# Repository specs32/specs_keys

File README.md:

# specs_keys - REV 1 (confirmed working, typing on it now :D)

### TKL ISO keyboard based on an g80-3000HAD running QMK

15 Years ago I found 2 g80-3000 HAD Keyboards in the trash, one broke lately so I designed a PCB to mount these sweet sweet Cherry MX black switches on it.

The base plate is the acryl plate from an old TFT Monitor cut to size and sanded. (roughly)
Between PCB and baseplate is some foamy stuff for dampening.

So, except the pcb and the mcu and a couple smd parts this thing is completly salvaged from trash.

Overall cost per board with parts (except switches) : 18 €

(8 € per PCB and 10 € for SMD parts, rest is salvaged, so this is probably the cheapest build out there)

Features  :
  - ATMega 32U4 @ 8 MHz (why the crystal ... such a waste, sigh)
  - USB-C jack **with FUSE and full ESD protection** (gnd vcc d+ d-)
  - MOSFET controlled bottom backlighting pads for 14 LEDs with resistors plus 2 extra 2mm connectors for lantern style lightning
  - Scroll and caps indicators (active low atm.. I kinda like it)
  - SPI interface and reset
  - 340mA overall power consumption with full lights (I put in UV / pink LEDs and 14 Ω Resistors)

the QMK layout and config can be found here :  https://github.com/specs32/specs_keys/tree/main/specskeys

I hex the MCU with avrdude from cli after QMK compile, somehow I had trouble with bootloaders all my life ^^ (also safer this way .. I guess;))

> qmk_firmware [master]× » avrdude -c usbasp -p m32u4 -B10 -U lfuse:w:0xD2:m -U hfuse:w:0x98:m -U efuse:w:0xFF:m

> qmk_firmware [master]× » avrdude -c usbasp -pm32u4 -B10 -Uflash:w:.build/specskeys_default.hex                

designed with kicad nightly Version: (5.99.0-10004-g132ec37b56), release build
and some gimp

credits :

- evyd13 and ebastler (to modify the g80-3003 design was my initial attempt but I did build the PCB from scratch then)
- the designers of evil80 (whoever that might be, couldn't find any infos on that) I used some of their qmk layout information as info for mine

License on the KiCAD Design files : ♥ CC-BY-SA-4.0

All other parts of this build inherit their Licenses from their origin.

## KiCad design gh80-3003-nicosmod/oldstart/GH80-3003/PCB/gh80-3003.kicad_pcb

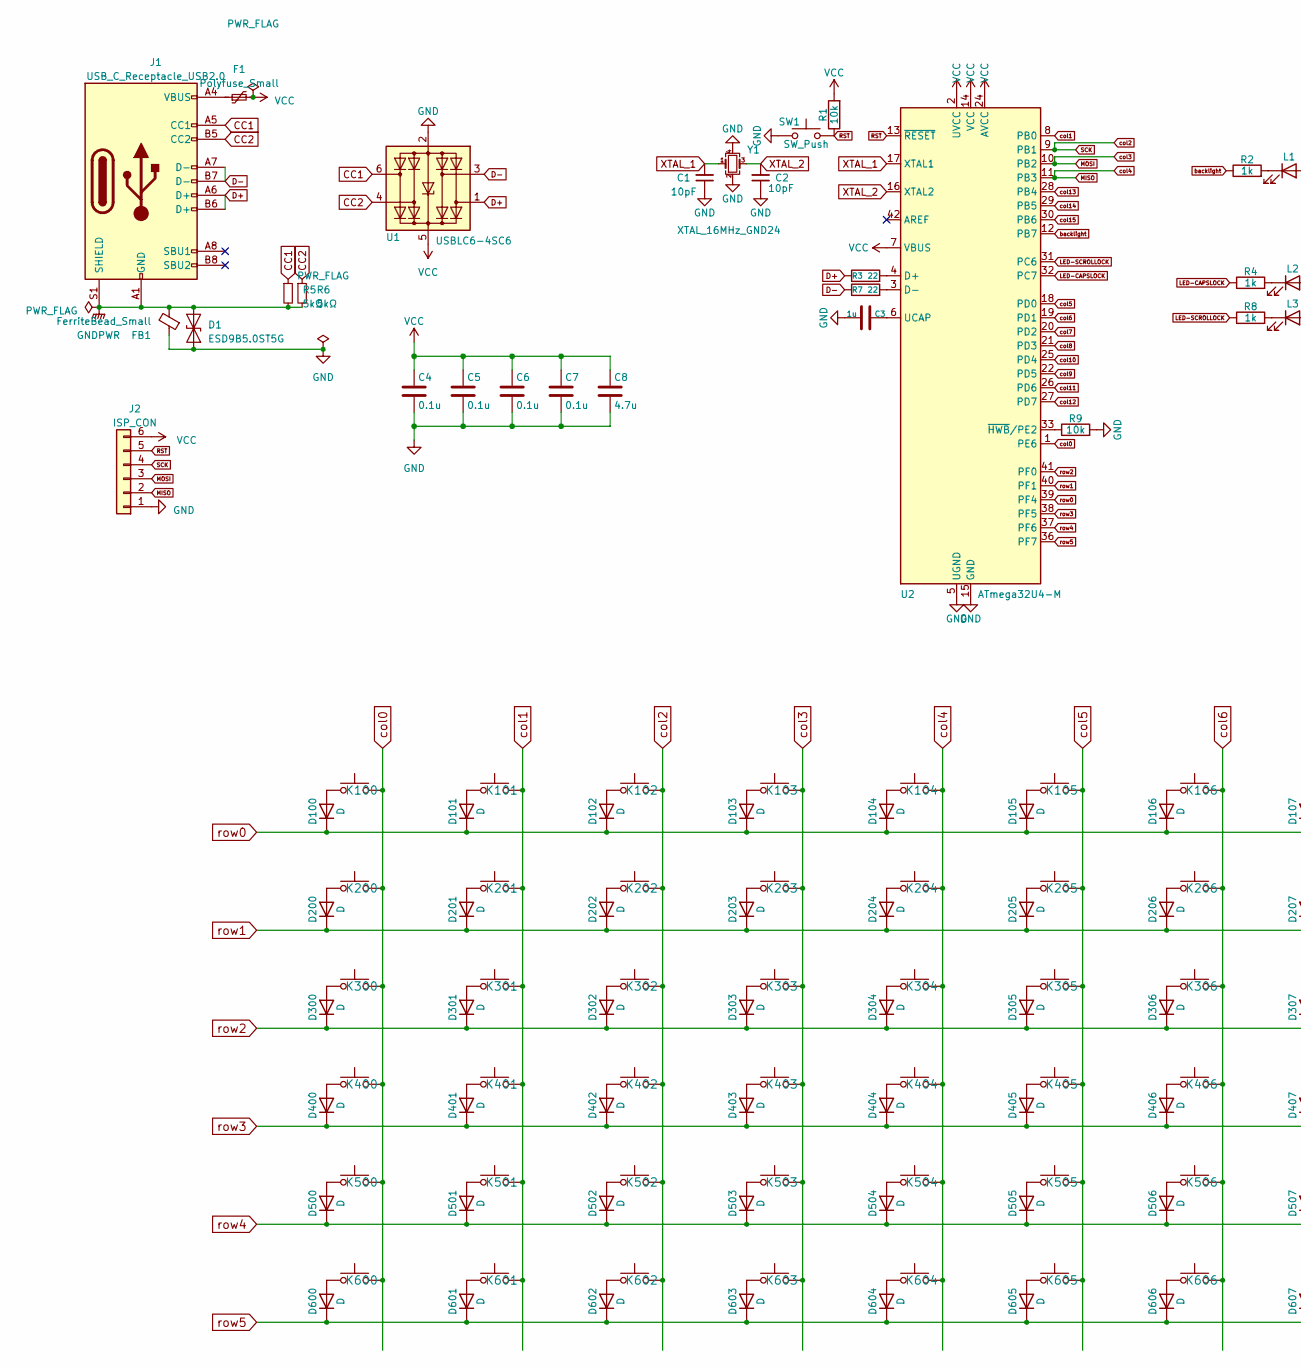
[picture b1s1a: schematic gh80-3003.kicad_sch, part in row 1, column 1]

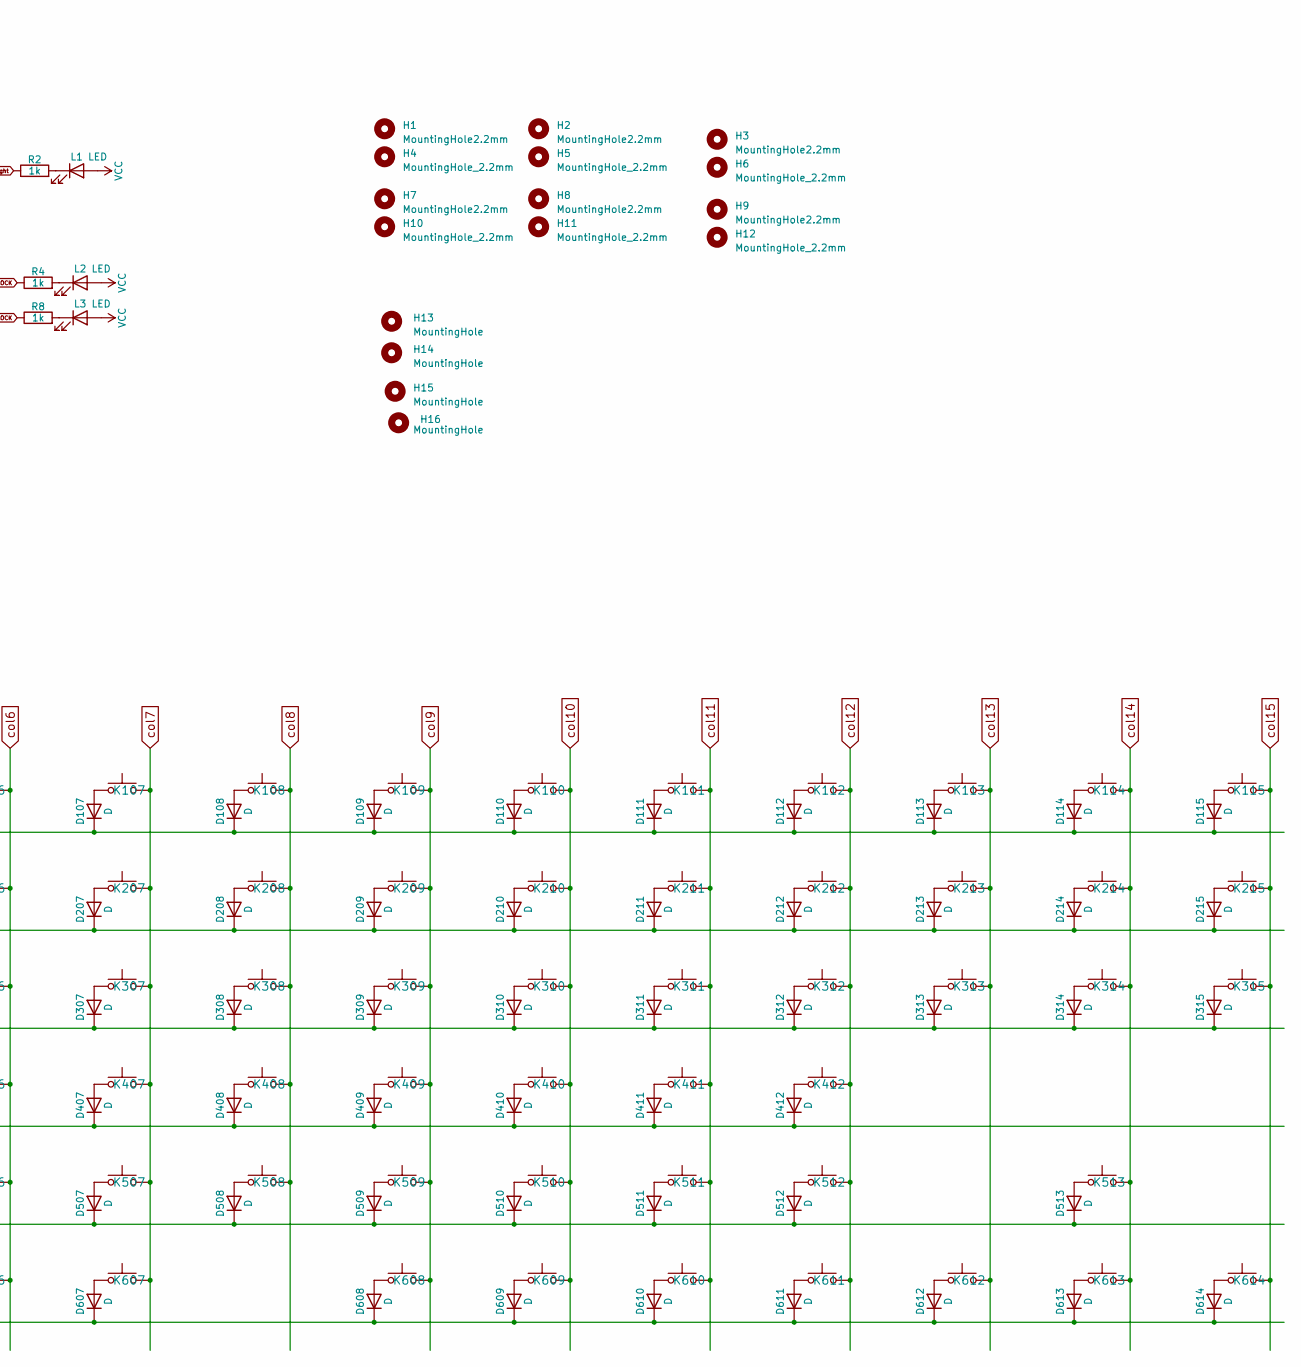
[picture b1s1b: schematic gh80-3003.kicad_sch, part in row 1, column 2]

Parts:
C1, C2: 10pF; C_0603_1608Metric_Pad1.08x0.95mm_HandSolder
C3: 1u; C_0805_2012Metric_Pad1.18x1.45mm_HandSolder
C4, C5, C6, C7: 0.1u; C_0603_1608Metric
C8: 4.7u; C_0805_2012Metric_Pad1.18x1.45mm_HandSolder
D1: ESD9B5.0ST5G; D_0402_1005Metric_Pad0.77x0.64mm_HandSolder
D100, D101, D102, D103, D104, D105, D106, D107, D108, D109, D110, D111, D112, D113, D114, D115, D200, D201, D202, D203, D204, D205, D206, D207, D208, D209, D210, D211, D212, D213, D214, D215, D300, D301, D302, D303, D304, D305, D306, D307, D308, D309, D310, D311, D312, D313, D314, D315, D400, D401, D402, D403, D404, D405, D406, D407, D408, D409, D410, D411, D412, D500, D501, D502, D503, D504, D505, D506, D507, D508, D509, D510, D511, D512, D513, D600, D601, D602, D603, D604, D605, D606, D607, D608, D609, D610, D611, D612, D613, D614: D; D_0402_1005Metric_Pad0.77x0.64mm_HandSolder
F1: Polyfuse_Small; R_0805_2012Metric_Pad1.20x1.40mm_HandSolder
FB1: FerriteBead_Small; R_0805_2012Metric_Pad1.20x1.40mm_HandSolder
H1, H2, H3, H7, H8, H9: MountingHole2.2mm; MountingHole_2.2mm_M2
H4, H5, H6, H10, H11, H12: MountingHole_2.2mm; MountingHole_2.2mm_M2
H13, H14, H15, H16: MountingHole; MountingHole_5.3mm_M5_ISO14580
J1: USB_C_Receptacle_USB2.0; USB_C_Receptacle_JAE_DX07S016JA1R1500
J2: ISP_CON; Conn_01x06_SMD_2mm
K100, K101, K102, K103, K104, K105, K106, K107, K108, K109, K110, K111, K112, K113, K114, K115, K200, K201, K202, K203, K204, K205, K206, K207, K208, K209, K210, K211, K212, K213, K214, K215, K300, K301, K302, K303, K304, K305, K306, K307, K308, K309, K310, K311, K312, K313, K314, K315, K400, K401, K402, K403, K404, K405, K406, K407, K408, K409, K410, K411, K412, K500, K501, K502, K503, K504, K505, K506, K507, K508, K509, K510, K511, K512, K513, K600, K605, K606, K607, K608, K609, K610, K611, K612, K613, K614: SW_Push; SW_Cherry_MX_1.00u_PCB
K601, K603: SW_Push; SW_Cherry_MX_1.50u_PCB
K602: SW_Push; SW_Cherry_MX_2.00u_PCB
K604: SW_Push; SW_Cherry_MX_1.75u_PCB
L1, L2, L3: LED; LED_0805_2012Metric_Pad1.15x1.40mm_HandSolder
R1, R9: 10k; R_0603_1608Metric
R2, R4, R8: 1k; R_0603_1608Metric
R3, R7: 22; R_0603_1608Metric
R5, R6: 5kΩ; R_0603_1608Metric
SW1: SW_Push; SW_SPST_TL3342
U1: USBLC6-4SC6; SOT-23-6
U2: ATmega32U4-M; QFN-44-1EP_7x7mm_P0.5mm_EP5.2x5.2mm
Y1: XTAL_16MHz_GND24; Crystal_SMD_2016-4Pin_2.0x1.6mm

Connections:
CC1: J1.A5 (CC1), R5.1, U1.6 (I/O4)
CC2: J1.B5 (CC2), R6.1, U1.4 (I/O3)
D+: J1.A6 (D+), J1.B6 (D+), R3.1, U1.1 (I/O1)
D-: J1.A7 (D-), J1.B7 (D-), R7.1, U1.3 (I/O2)
GND: C1.1, C2.1, C3.2, C4.2, C5.2, C6.2, C7.2, C8.2, D1.1 (A1), FB1.1, J2.1, R9.2, SW1.1, U1.2 (GND), U2.5 (UGND), U2.15 (GND), U2.23 (GND), U2.35 (GND), U2.43 (GND), U2.45 (GND), Y1.2, Y1.4
GNDPWR: D1.2 (A2), FB1.2, J1.A1 (GND), J1.A12 (GND), J1.B1 (GND), J1.B12 (GND), J1.S1 (SHIELD), R5.2, R6.2
LED-CAPSLOCK: R4.1, U2.32 (PC7)
LED-SCROLLOCK: R8.1, U2.31 (PC6)
MISO: J2.2, K104.1, K204.1, K304.1, K404.1, K504.1, K604.1, U2.11 (PB3)
MOSI: J2.3, K103.1, K203.1, K303.1, K403.1, K503.1, K603.1, U2.10 (PB2)
unnamed: C3.1, U2.6 (UCAP)
unnamed: D100.2 (A), K100.2
unnamed: D101.2 (A), K101.2
unnamed: D102.2 (A), K102.2
unnamed: D103.2 (A), K103.2
unnamed: D104.2 (A), K104.2
unnamed: D105.2 (A), K105.2
unnamed: D106.2 (A), K106.2
unnamed: D107.2 (A), K107.2
unnamed: D108.2 (A), K108.2
unnamed: D109.2 (A), K109.2
unnamed: D110.2 (A), K110.2
unnamed: D111.2 (A), K111.2
unnamed: D112.2 (A), K112.2
unnamed: D113.2 (A), K113.2
unnamed: D114.2 (A), K114.2
unnamed: D115.2 (A), K115.2
unnamed: D200.2 (A), K200.2
unnamed: D201.2 (A), K201.2
unnamed: D203.2 (A), K203.2
unnamed: D205.2 (A), K205.2
unnamed: D206.2 (A), K206.2
unnamed: D207.2 (A), K207.2
unnamed: D209.2 (A), K209.2
unnamed: D210.2 (A), K210.2
unnamed: D211.2 (A), K211.2
unnamed: D212.2 (A), K212.2
unnamed: D213.2 (A), K213.2
unnamed: D214.2 (A), K214.2
unnamed: D215.2 (A), K215.2
unnamed: D300.2 (A), K300.2
unnamed: D301.2 (A), K301.2
unnamed: D302.2 (A), K302.2
unnamed: D303.2 (A), K303.2
unnamed: D304.2 (A), K304.2
unnamed: D305.2 (A), K305.2
unnamed: D306.2 (A), K306.2
unnamed: D307.2 (A), K307.2
unnamed: D308.2 (A), K308.2
unnamed: D309.2 (A), K309.2
unnamed: D310.2 (A), K310.2
unnamed: D311.2 (A), K311.2
unnamed: D312.2 (A), K312.2
unnamed: D313.2 (A), K313.2
unnamed: D314.2 (A), K314.2
unnamed: D315.2 (A), K315.2
unnamed: D400.2 (A), K400.2
unnamed: D401.2 (A), K401.2
unnamed: D402.2 (A), K402.2
unnamed: D403.2 (A), K403.2
unnamed: D404.2 (A), K404.2
unnamed: D405.2 (A), K405.2
unnamed: D406.2 (A), K406.2
unnamed: D407.2 (A), K407.2
unnamed: D408.2 (A), K408.2
unnamed: D409.2 (A), K409.2
unnamed: D410.2 (A), K410.2
unnamed: D411.2 (A), K411.2
unnamed: D412.2 (A), K412.2
unnamed: D500.2 (A), K500.2
unnamed: D501.2 (A), K501.2
unnamed: D502.2 (A), K502.2
unnamed: D503.2 (A), K503.2
unnamed: D504.2 (A), K504.2
unnamed: D505.2 (A), K505.2
unnamed: D506.2 (A), K506.2
unnamed: D507.2 (A), K507.2
unnamed: D508.2 (A), K508.2
unnamed: D509.2 (A), K509.2
unnamed: D510.2 (A), K510.2
unnamed: D511.2 (A), K511.2
unnamed: D512.2 (A), K512.2
unnamed: D513.2 (A), K513.2
unnamed: D600.2 (A), K600.2
unnamed: D601.2 (A), K601.2
unnamed: D602.2 (A), K602.2
unnamed: D603.2 (A), K603.2
unnamed: D604.2 (A), K604.2
unnamed: D605.2 (A), K605.2
unnamed: D606.2 (A), K606.2
unnamed: D607.2 (A), K607.2
unnamed: D608.2 (A), K608.2
unnamed: D609.2 (A), K609.2
unnamed: D610.2 (A), K610.2
unnamed: D611.2 (A), K611.2
unnamed: D612.2 (A), K612.2
unnamed: D613.2 (A), K613.2
unnamed: D614.2 (A), K614.2
unnamed: F1.1, J1.A4 (VBUS), J1.A9 (VBUS), J1.B4 (VBUS), J1.B9 (VBUS)
unnamed: D202.2 (A), K202.2
unnamed: D204.2 (A), K204.2
unnamed: D208.2 (A), K208.2
unnamed: L1.1 (K), R2.2
unnamed: L2.1 (K), R4.2
unnamed: L3.1 (K), R8.2
unnamed: R3.2, U2.4 (D+)
unnamed: R7.2, U2.3 (D-)
unnamed: R9.1, U2.33 (~HWB~/PE2)
RST: J2.5, R1.1, SW1.2, U2.13 (~RESET)
SCK: J2.4, K102.1, K202.1, K302.1, K402.1, K502.1, K602.1, U2.9 (PB1)
VCC: C4.1, C5.1, C6.1, C7.1, C8.1, F1.2, J2.6, L1.2 (A), L2.2 (A), L3.2 (A), R1.2, U1.5 (VBUS), U2.2 (UVCC), U2.7 (VBUS), U2.14 (VCC), U2.24 (AVCC), U2.34 (VCC), U2.44 (AVCC)
XTAL_1: C1.2, U2.17 (XTAL1), Y1.1
XTAL_2: C2.2, U2.16 (XTAL2), Y1.3
backlight: R2.1, U2.12 (PB7)
col0: K100.1, K200.1, K300.1, K400.1, K500.1, K600.1, U2.1 (PE6)
col1: K101.1, K201.1, K301.1, K401.1, K501.1, K601.1, U2.8 (PB0)
col5: K105.1, K205.1, K305.1, K405.1, K505.1, K605.1, U2.18 (PD0)
col6: K106.1, K206.1, K306.1, K406.1, K506.1, K606.1, U2.19 (PD1)
col7: K107.1, K207.1, K307.1, K407.1, K507.1, K607.1, U2.20 (PD2)
col8: K108.1, K208.1, K308.1, K408.1, K508.1, U2.21 (PD3)
col9: K109.1, K209.1, K309.1, K409.1, K509.1, K608.1, U2.22 (PD5)
col10: K110.1, K210.1, K310.1, K410.1, K510.1, K609.1, U2.25 (PD4)
col11: K111.1, K211.1, K311.1, K411.1, K511.1, K610.1, U2.26 (PD6)
col12: K112.1, K212.1, K312.1, K412.1, K512.1, K611.1, U2.27 (PD7)
col13: K113.1, K213.1, K313.1, K612.1, U2.28 (PB4)
col14: K114.1, K214.1, K314.1, K513.1, K613.1, U2.29 (PB5)
col15: K115.1, K215.1, K315.1, K614.1, U2.30 (PB6)
row0: D100.1 (K), D101.1 (K), D102.1 (K), D103.1 (K), D104.1 (K), D105.1 (K), D106.1 (K), D107.1 (K), D108.1 (K), D109.1 (K), D110.1 (K), D111.1 (K), D112.1 (K), D113.1 (K), D114.1 (K), D115.1 (K), U2.39 (PF4)
row1: D200.1 (K), D201.1 (K), D202.1 (K), D203.1 (K), D204.1 (K), D205.1 (K), D206.1 (K), D207.1 (K), D208.1 (K), D209.1 (K), D210.1 (K), D211.1 (K), D212.1 (K), D213.1 (K), D214.1 (K), D215.1 (K), U2.40 (PF1)
row2: D300.1 (K), D301.1 (K), D302.1 (K), D303.1 (K), D304.1 (K), D305.1 (K), D306.1 (K), D307.1 (K), D308.1 (K), D309.1 (K), D310.1 (K), D311.1 (K), D312.1 (K), D313.1 (K), D314.1 (K), D315.1 (K), U2.41 (PF0)
row3: D400.1 (K), D401.1 (K), D402.1 (K), D403.1 (K), D404.1 (K), D405.1 (K), D406.1 (K), D407.1 (K), D408.1 (K), D409.1 (K), D410.1 (K), D411.1 (K), D412.1 (K), U2.38 (PF5)
row4: D500.1 (K), D501.1 (K), D502.1 (K), D503.1 (K), D504.1 (K), D505.1 (K), D506.1 (K), D507.1 (K), D508.1 (K), D509.1 (K), D510.1 (K), D511.1 (K), D512.1 (K), D513.1 (K), U2.37 (PF6)
row5: D600.1 (K), D601.1 (K), D602.1 (K), D603.1 (K), D604.1 (K), D605.1 (K), D606.1 (K), D607.1 (K), D608.1 (K), D609.1 (K), D610.1 (K), D611.1 (K), D612.1 (K), D613.1 (K), D614.1 (K), U2.36 (PF7)

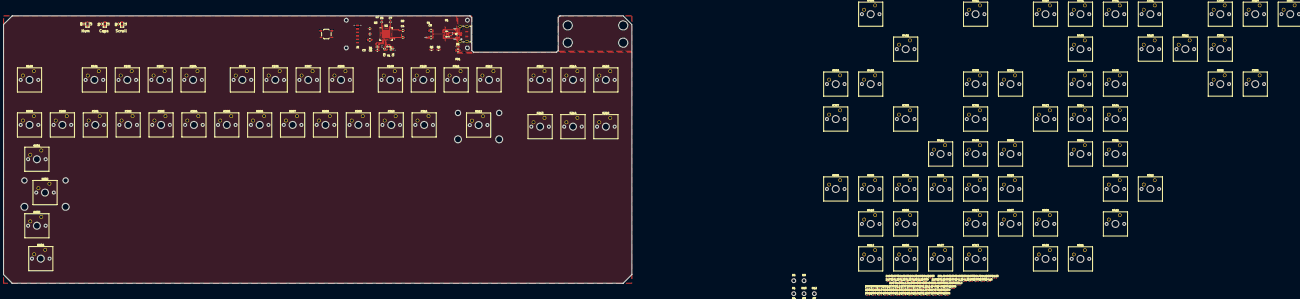
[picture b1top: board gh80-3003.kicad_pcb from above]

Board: 4 copper layers, 363.0 x 154.5 mm, 225 parts (0 on the bottom side), 133 nets.

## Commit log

2021-04-06 init
    HARDWARE IS TO BE TESTED !!!!
2021-05-04 QMK-Firmware
    qmk config for specs keys
